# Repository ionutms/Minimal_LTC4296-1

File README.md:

# Minimal_LTC4296-1

## Overview

This repository contains a minimal KiCad design project for the Analog Devices LTC4296-1, a 5-port SPoE (Single-Pair Power over Ethernet) PSE (Power Sourcing Equipment) controller. The project includes schematic designs and PCB layout files for implementing this versatile multi-port PoE controller.

## Disclaimer

> [!NOTE]
> This project is provided "as is" and without any warranty, express or implied. For more details, please see the [LICENSE](LICENSE) file.

## About the LTC4296-1

The LTC4296-1 from Analog Devices is a 5-port SPoE (Single-Pair Power over Ethernet) PSE controller designed for building and factory automation applications. It provides power sourcing equipment functionality for IEEE 802.3cg-compliant single-pair Ethernet systems.

Key features include:

- **5 Independent PSE Ports:** Controls up to five independent PSE ports with individual monitoring and control.
- **Wide Input Supply Range:** Operates from 6 V to 60 V, supporting both 24 V and 54 V systems.
- **IEEE 802.3cg Compliant:** Supports Single-Pair Power over Ethernet (SPoE) standard with power classes 10 through 15.
- **SCCP Support:** Supports Serial Communication Classification Protocol (SCCP) with external microcontroller for PD classification.
- **SPI Interface:** SPI bus interface with PEC (Packet Error Code) protection for digital control and monitoring.
- **Advanced Protection:** Features adjustable source and return electronic circuit breakers, high-side circuit breakers with foldback, and analog current limit (ACL).
- **Low Power Consumption:** Ultra-low input supply current of 52 μA (typ) in sleep state and 51 μA (typ) in disabled state.
- **Telemetry:** Voltage, current, and temperature telemetry with per-port power-good comparators.
- **Operating Temperature Range:** -40°C to +125°C.
- **Package:** Available in a 48-lead plastic QFN package (7 mm × 7 mm).

## Project Structure

```
minimal_ltc4296-1/
├── minimal_ltc4296-1.kicad_pro                     # Project configuration file
├── minimal_ltc4296-1.kicad_sch                     # Main schematic file
├── SCCP Circuit 0.kicad_sch                        # SCCP circuit schematic
├── minimal_ltc4296-1.kicad_pcb                     # PCB layout file
├── fp-lib-table                                    # Footprint library table
├── sym-lib-table                                   # Symbol library table
├── docs/                                           # Documentation files
│   ├── bom/                                        # Bill of Materials
│   │   └── minimal_ltc4296-1_ibom.html             # Interactive BOM file
│   ├── pictures/                                   # Images and photos
│   │   ├── 1_minimal_ltc4296-1_side.png            # Side view of PCB
│   │   ├── 2_minimal_ltc4296-1_top.png             # Top view of PCB
│   │   ├── 3_minimal_ltc4296-1_bottom.png          # Bottom view of PCB
│   │   ├── 4_minimal_ltc4296-1_left.png            # Left view of PCB
│   │   ├── 5_minimal_ltc4296-1_right.png           # Right view of PCB
│   │   ├── 6_minimal_ltc4296-1_front.png           # Front view of PCB
│   │   ├── 7_minimal_ltc4296-1_back.png            # Back view of PCB
│   │   └── 8_minimal_ltc4296-1_test.png            # Test view of PCB
│   └── schematics/                                 # Schematic PDF exports
│       └── minimal_ltc4296-1_schematics.pdf        # Complete schematics PDF
└── KiCAD_Symbols_Generator/                        # Submodule for symbol generation from CSV data
```

## Project Features

This design provides a minimal implementation of the LTC4296-1 with:

- 5-port PSE controller configuration
- SPI interface for digital control
- SCCP classification support
- Per-port current monitoring and protection
- Standard footprint for the 48-lead QFN package

## Getting Started

### Prerequisites

- [KiCad EDA](https://www.kicad.org/) version 9.0 or later installed on your system
- Git (for cloning the repository and submodule management)

### Opening the Project

1. **Clone the repository** (including submodules):
   ```bash
   git clone --recursive https://github.com/ionutms/Minimal_LTC4296-1.git
   ```

   If you've already cloned the repository without submodules, initialize them with:
   ```bash
   git submodule init
   git submodule update
   ```

2. **Open the project in KiCad**:
   - Launch KiCad
   - Click "Open Existing Project"
   - Navigate to the cloned repository folder
   - Select the `minimal_ltc4296-1.kicad_pro` file

3. **Explore the design**:
   - Open the schematic editor to view the circuit design
   - Open the PCB editor to view the board layout
   - Review the symbol and footprint libraries used in the design

### Project Files

- **Main schematic**: `minimal_ltc4296-1.kicad_sch` - Contains the primary circuit design with the LTC4296-1 and support components
- **SCCP schematic**: `SCCP Circuit 0.kicad_sch` - SCCP circuit implementation for PD classification
- **PCB layout**: `minimal_ltc4296-1.kicad_pcb` - Physical board design file with proper component placement
- **Project configuration**: `minimal_ltc4296-1.kicad_pro` - KiCad project settings

## Dependencies

This project has the following dependencies:

### 1. KiCAD Symbols Generator

This repository uses [KiCAD_Symbols_Generator](https://github.com/ionutms/KiCAD_Symbols_Generator) as a submodule for custom symbol generation.

To initialize the submodule after cloning this repository:

```bash
git submodule update --init --recursive
```

### 2. 3D Models

This project requires the [3D_Models_Vault](https://github.com/ionutms/3D_Models_Vault) repository for 3D models.

#### Setup for KiCAD 9:

1. Clone the 3D models repository:
   ```bash
   git clone https://github.com/ionutms/3D_Models_Vault.git
   ```

2. In KiCAD 9, add an environment variable:
   - Variable name: `KICAD9_3D_MODELS_VAULT`
   - Variable value: Full path to where you cloned the 3D_Models_Vault repository

## Usage

After setting up the dependencies, open the project in KiCad 9 to access all features including the 3D models.

## Symbol Generator Submodule

This project includes the KiCAD_Symbols_Generator as a submodule, which provides tools for generating KiCad symbols from CSV data files. For more information on using this tool, see the [KiCAD_Symbols_Generator documentation](minimal_ltc4296-1/KiCAD_Symbols_Generator/README.md).

## Documentation

The `docs` folder contains:
- Schematic PDF exports
- Images and photos of the design

## Visuals

The following images showcase the PCB design from different perspectives:

*Top View of the PCB*

*Side View of the PCB*

*Bottom View of the PCB*

*Left View of the PCB*

*Right View of the PCB*

*Front View of the PCB*

*Back View of the PCB*

## License

This project is licensed under the MIT License - see the [LICENSE](LICENSE) file for details.

## References

- [LTC4296-1 Datasheet](https://www.analog.com/media/en/technical-documentation/data-sheets/ltc4296-1.pdf)
- [LTC4296-1 Product Page](https://www.analog.com/en/products/ltc4296-1.html)
- [KiCad EDA](https://www.kicad.org/)

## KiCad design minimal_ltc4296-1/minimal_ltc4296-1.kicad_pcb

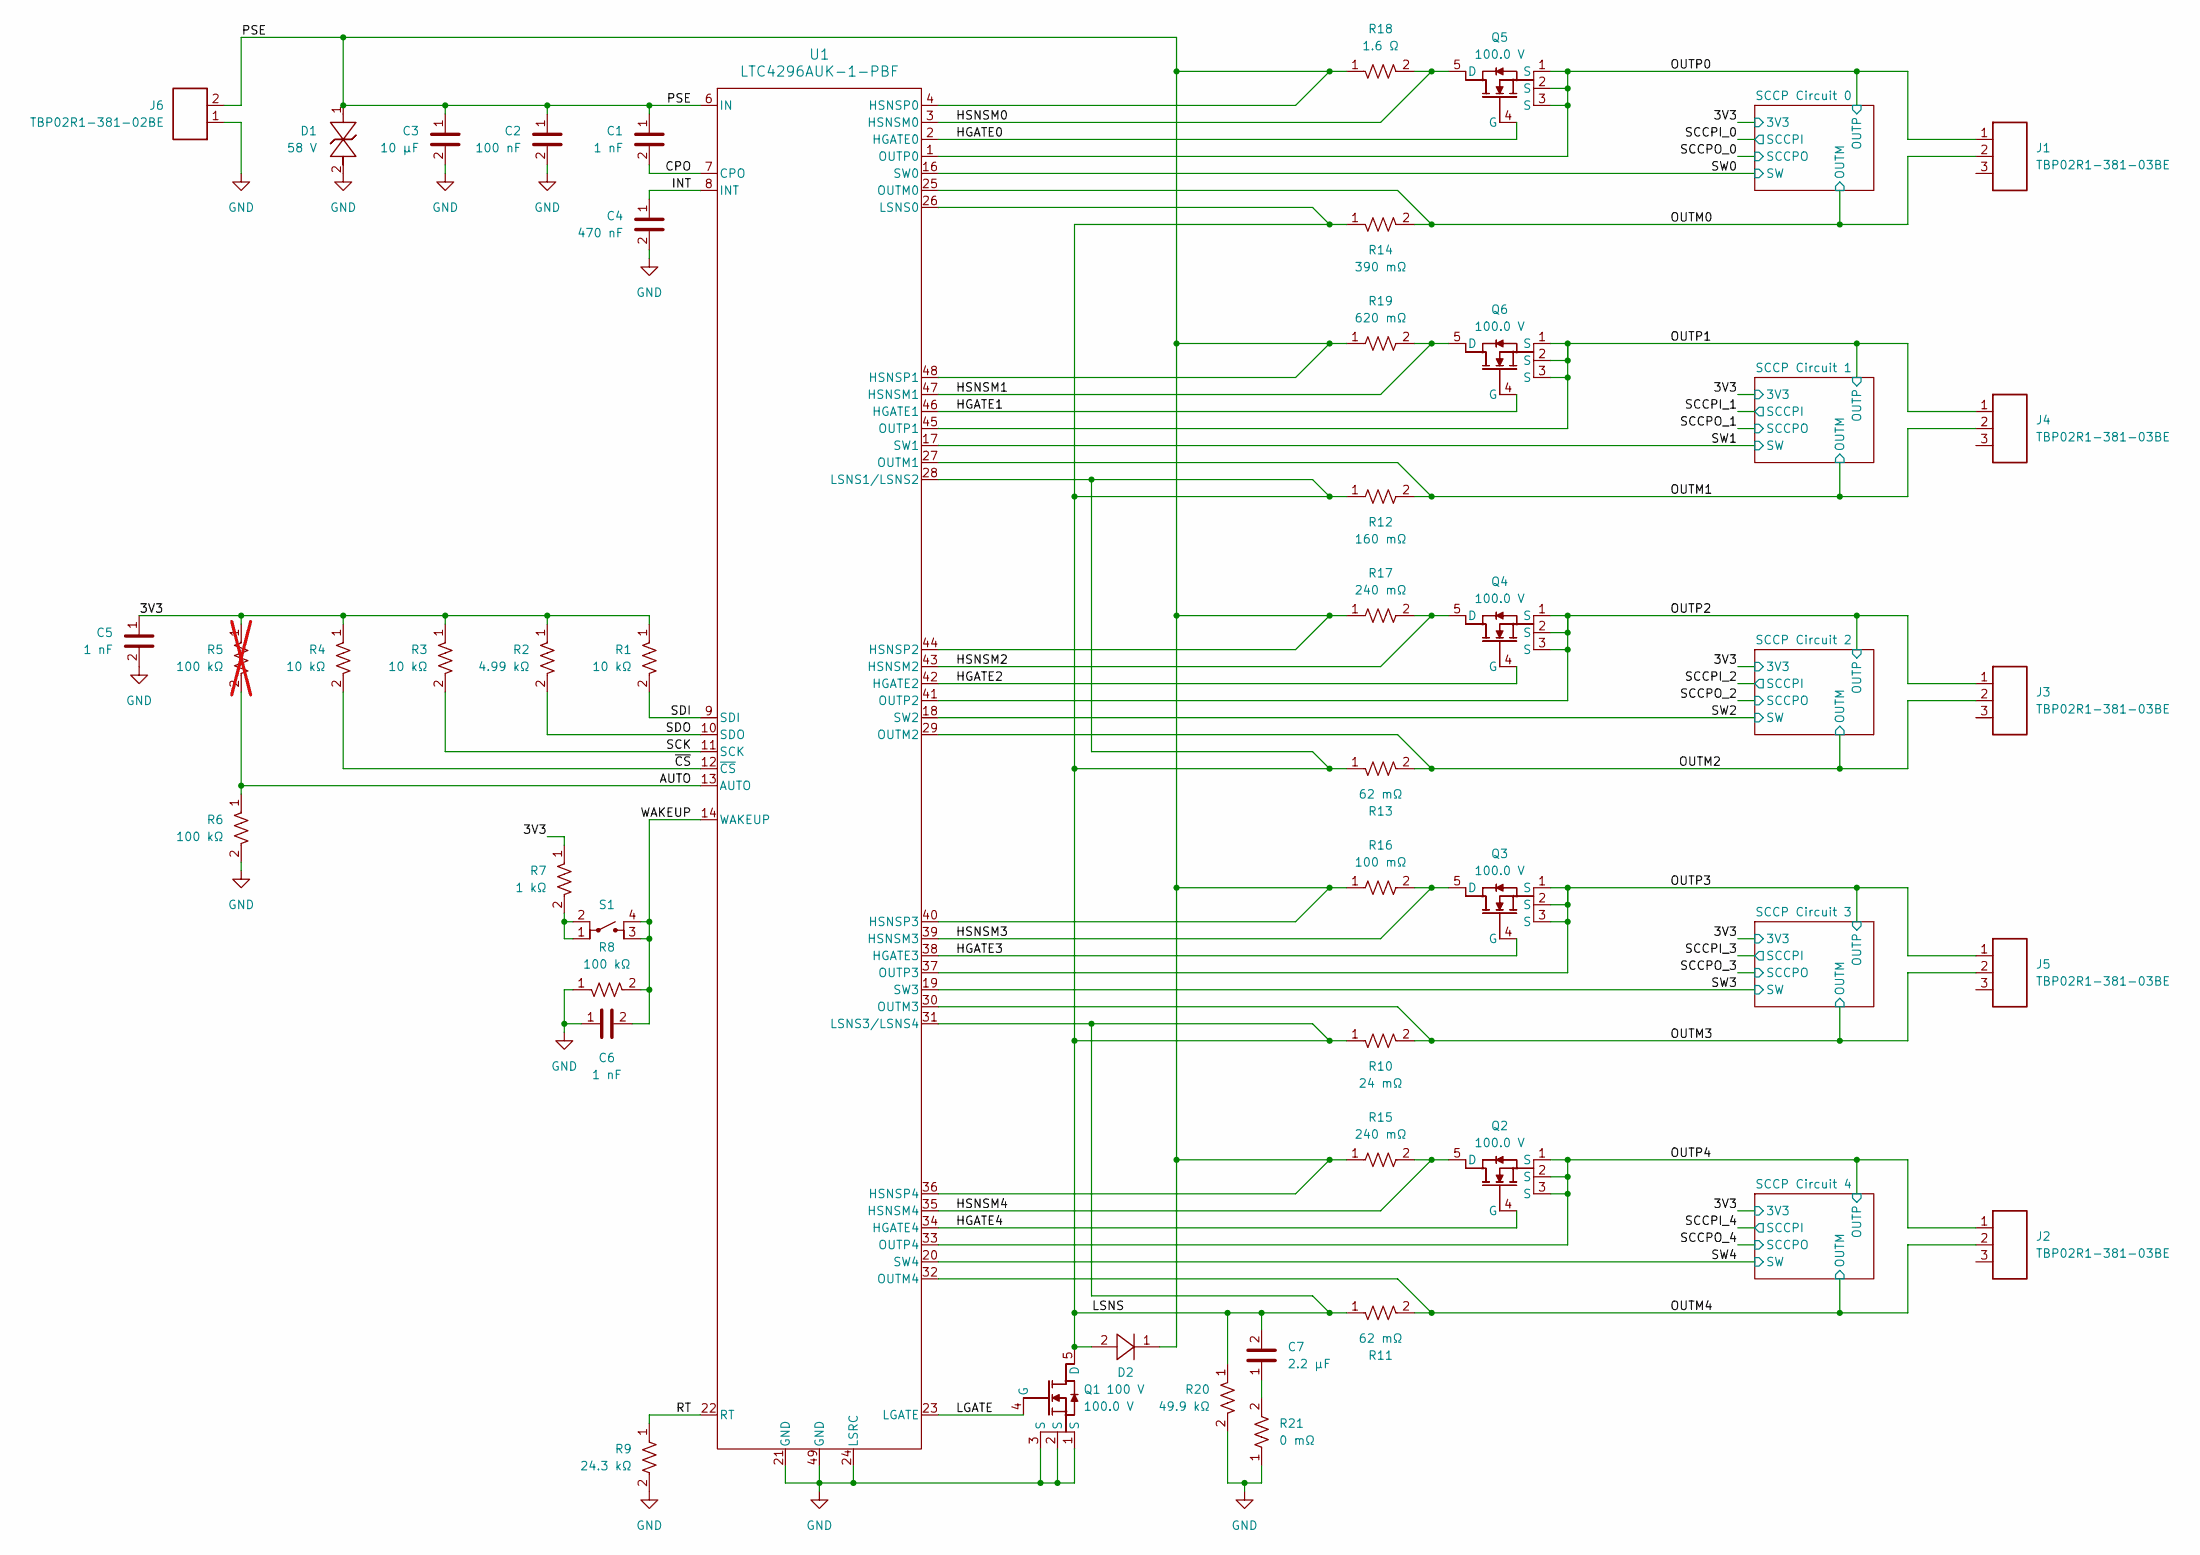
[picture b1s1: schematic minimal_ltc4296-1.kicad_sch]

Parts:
C1: 1 nF; C_0402_1005Metric; Tolerance 10%; Voltage Rating 100V; MPN C1005X7S2A102K050BB
C2: 100 nF; C_0603_1608Metric; Tolerance 10%; Voltage Rating 100V; MPN C1608X7S2A104K080AB
C3: 10 µF; C_1210_250_3225Metric; Tolerance 10%; Voltage Rating 100V; MPN GRM32EC72A106KE05L
C4: 470 nF; C_0402_1005Metric; Tolerance 10%; Voltage Rating 25V; MPN C1005X5R1E474K050BB
C5, C6: 1 nF; C_0402_1005Metric; Tolerance 10%; Voltage Rating 50V; MPN GCM155R71H102KA37D
C7: 2.2 µF; C_0805_2012Metric; Tolerance 10%; Voltage Rating 100V; MPN CGA4J1X7R2A225K125AC
D1: 58 V; DO-214AA; MPN SMBJ58CA
D2: 100 V; SMA; MPN S1B-13-F
J1, J2, J3, J4, J5: TBP02R1-381-03BE; Current Rating (A) 8.0; Voltage Rating (V) 300; MPN TBP02R1-381-03BE
J6: TBP02R1-381-02BE; Current Rating (A) 8.0; Voltage Rating (V) 300; MPN TBP02R1-381-02BE
Q1, Q2, Q4, Q5: 100.0 V; LFPAK33-8; MPN PSMN075-100MSEX
Q3, Q6: 100.0 V; LFPAK33-8; MPN PSMN040-100MSEX
R1, R3, R4: 10 kΩ; R_0402_1005Metric; Tolerance 1%; Voltage Rating 50V; MPN ERJ-2RKF1002X
R2: 4.99 kΩ; R_0402_1005Metric; Tolerance 1%; Voltage Rating 50V; MPN ERJ-2RKF4991X
R5: 100 kΩ; R_0402_1005Metric; Tolerance 1%; Voltage Rating 50V; MPN ERJ-2RKF1003X; not fitted
R6, R8: 100 kΩ; R_0402_1005Metric; Tolerance 1%; Voltage Rating 50V; MPN ERJ-2RKF1003X
R7: 1 kΩ; R_0402_1005Metric; Tolerance 1%; Voltage Rating 50V; MPN ERJ-2RKF1001X
R9: 24.3 kΩ; R_0402_1005Metric; Tolerance 1%; Voltage Rating 50V; MPN ERJ-2RKF2432X
R10: 24 mΩ; R_0612_1632Metric; Tolerance 1%; MPN ERJ-B2CFR024V
R11, R13: 62 mΩ; R_0612_1632Metric; Tolerance 1%; MPN PRL1632-R062-F-T1
R12: 160 mΩ; R_0612_1632Metric; Tolerance 1%; MPN ERJ-B2CFR16V
R14: 390 mΩ; R_0612_1632Metric; Tolerance 1%; MPN ERJ-B2BFR39V
R15, R17: 240 mΩ; R_0612_1632Metric; Tolerance 1%; MPN ERJ-B2BFR24V
R16: 100 mΩ; R_0612_1632Metric; Tolerance 1%; MPN ERJ-B2CFR10V
R18: 1.6 Ω; R_0612_1632Metric; Tolerance 1%; MPN ERJ-B2BF1R6V
R19: 620 mΩ; R_0612_1632Metric; Tolerance 1%; MPN ERJ-B2BFR62V
R20: 49.9 kΩ; R_0805_2012Metric; Tolerance 1%; Voltage Rating 150V; MPN ERJ-6ENF4992V
R21: 0 mΩ; R_0805_2012Metric; Tolerance 5%; Voltage Rating 150V; MPN ERJ-6GEY0R00V
S1: TS21-34-035-BK-160-SMT-TR; TS21; MPN TS21-34-035-BK-160-SMT-TR
U1: LTC4296AUK-1-PBF; QFN48_05-08-7073_ADI; MPN LTC4296AUK-1-PBF

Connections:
/3V3: C5.1, R1.1, R2.1, R3.1, R4.1, R5.1, R7.1; also elsewhere on the board
/AUTO: R5.2, R6.1, U1.13 (AUTO)
/CPO: C1.2, U1.7 (CPO)
/HGATE0: Q5.4 (G), U1.2 (HGATE0)
/HGATE1: Q6.4 (G), U1.46 (HGATE1)
/HGATE2: Q4.4 (G), U1.42 (HGATE2)
/HGATE3: Q3.4 (G), U1.38 (HGATE3)
/HGATE4: Q2.4 (G), U1.34 (HGATE4)
/HSNSM0: Q5.5 (D), R18.2, U1.3 (HSNSM0)
/HSNSM1: Q6.5 (D), R19.2, U1.47 (HSNSM1)
/HSNSM2: Q4.5 (D), R17.2, U1.43 (HSNSM2)
/HSNSM3: Q3.5 (D), R16.2, U1.39 (HSNSM3)
/HSNSM4: Q2.5 (D), R15.2, U1.35 (HSNSM4)
/INT: C4.1, U1.8 (INT)
/LGATE: Q1.4 (G), U1.23 (LGATE)
/LSNS: C7.2, D2.2, Q1.5 (D), R10.1, R11.1, R12.1, R13.1, R14.1, R20.1, U1.26 (LSNS0), U1.28 (LSNS1/LSNS2), U1.31 (LSNS3/LSNS4)
/OUTM0: J1.2, R14.2, U1.25 (OUTM0); also elsewhere on the board
/OUTM1: J4.2, R12.2, U1.27 (OUTM1); also elsewhere on the board
/OUTM2: J3.2, R13.2, U1.29 (OUTM2); also elsewhere on the board
/OUTM3: J5.2, R10.2, U1.30 (OUTM3); also elsewhere on the board
/OUTM4: J2.2, R11.2, U1.32 (OUTM4); also elsewhere on the board
/OUTP0: J1.1, Q5.1 (S), Q5.2 (S), Q5.3 (S), U1.1 (OUTP0); also elsewhere on the board
/OUTP1: J4.1, Q6.1 (S), Q6.2 (S), Q6.3 (S), U1.45 (OUTP1); also elsewhere on the board
/OUTP2: J3.1, Q4.1 (S), Q4.2 (S), Q4.3 (S), U1.41 (OUTP2); also elsewhere on the board
/OUTP3: J5.1, Q3.1 (S), Q3.2 (S), Q3.3 (S), U1.37 (OUTP3); also elsewhere on the board
/OUTP4: J2.1, Q2.1 (S), Q2.2 (S), Q2.3 (S), U1.33 (OUTP4); also elsewhere on the board
/PSE: C1.1, C2.1, C3.1, D1.1, D2.1, J6.2, R15.1, R16.1, R17.1, R18.1, R19.1, U1.4 (HSNSP0), U1.6 (IN), U1.36 (HSNSP4), U1.40 (HSNSP3), U1.44 (HSNSP2), U1.48 (HSNSP1)
/RT: R9.1, U1.22 (RT)
/SCK: R3.2, U1.11 (SCK)
/SDI: R1.2, U1.9 (SDI)
/SDO: R2.2, U1.10 (SDO)
/SW0: U1.16 (SW0); also elsewhere on the board
/SW1: U1.17 (SW1); also elsewhere on the board
/SW2: U1.18 (SW2); also elsewhere on the board
/SW3: U1.19 (SW3); also elsewhere on the board
/SW4: U1.20 (SW4); also elsewhere on the board
/WAKEUP: C6.2, R8.2, S1.3, S1.4, U1.14 (WAKEUP)
/~CS: R4.2, U1.12 (~CS)
GND: C2.2, C3.2, C4.2, C5.2, C6.1, D1.2, J6.1, Q1.1 (S), Q1.2 (S), Q1.3 (S), R6.2, R8.1, R9.2, R20.2, R21.1, U1.21 (GND), U1.24 (LSRC), U1.49 (GND); also elsewhere on the board
unnamed: C7.1, R21.2
unnamed: R7.2, S1.1, S1.2

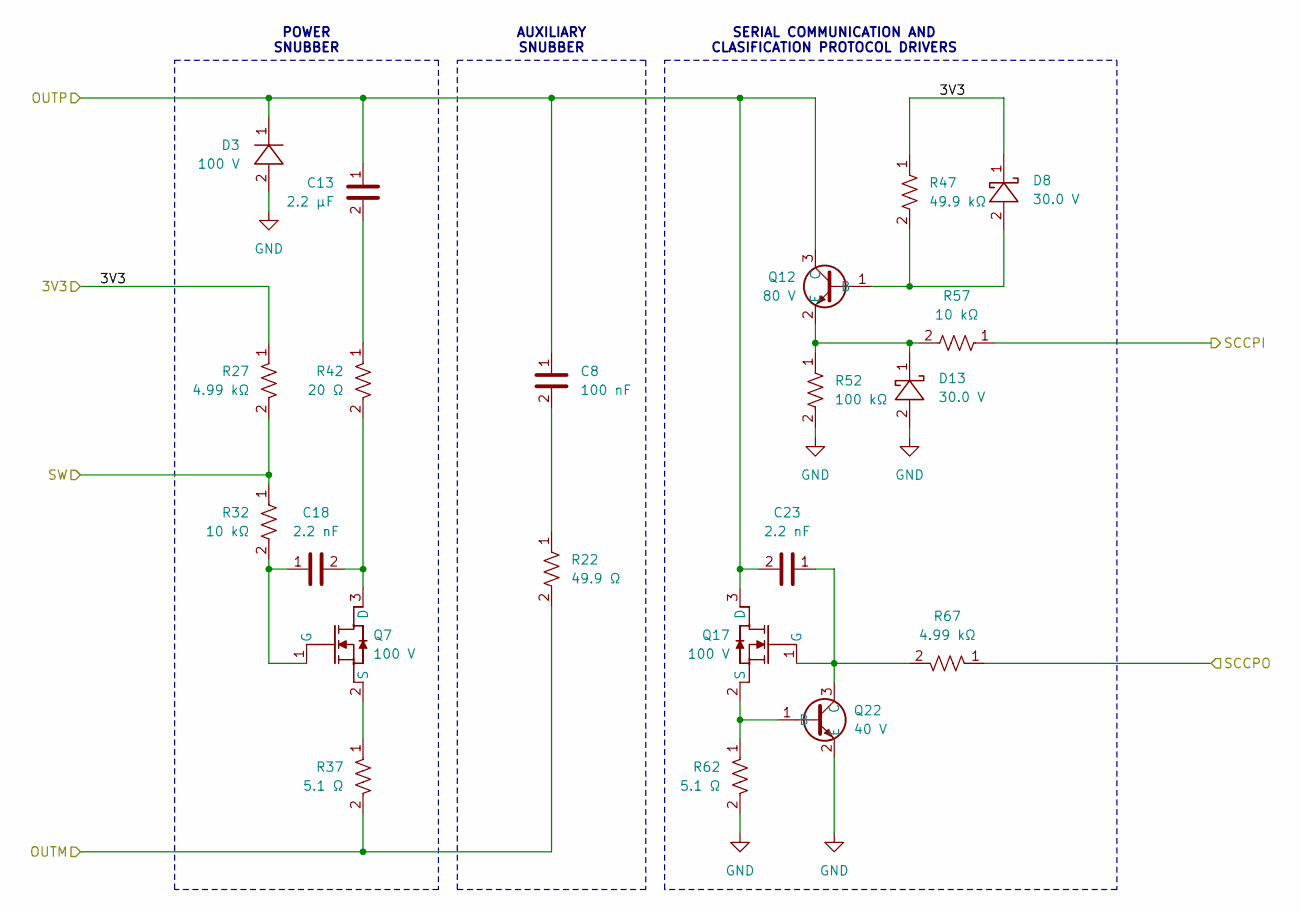
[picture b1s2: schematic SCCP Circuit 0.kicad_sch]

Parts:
C8: 100 nF; C_0603_1608Metric; Tolerance 10%; Voltage Rating 100V; MPN C1608X7S2A104K080AB
C13: 2.2 µF; C_0805_2012Metric; Tolerance 10%; Voltage Rating 100V; MPN CGA4J1X7R2A225K125AC
C18, C23: 2.2 nF; C_0402_1005Metric; Tolerance 10%; Voltage Rating 100V; MPN C1005X7S2A222K050BB
D3: 100 V; SMA; MPN S1B-13-F
D8, D13: 30.0 V; SOD323F; MPN BAT54WS-7-F
Q7, Q17: 100 V; SOT-323; MPN BSS123WQ-7-F
Q12: 80 V; SOT23-3; MPN MMBTA06-7-F
Q22: 40 V; SOT23-3; MPN MMBT3904LT3G
R22: 49.9 Ω; R_0603_1608Metric; Tolerance 1%; Voltage Rating 75V; MPN ERJ-3EKF49R9V
R27, R67: 4.99 kΩ; R_0402_1005Metric; Tolerance 1%; Voltage Rating 50V; MPN ERJ-2RKF4991X
R32, R57: 10 kΩ; R_0402_1005Metric; Tolerance 1%; Voltage Rating 50V; MPN ERJ-2RKF1002X
R37, R62: 5.1 Ω; R_1206_3216Metric; Tolerance 1%; Voltage Rating 200V; MPN RT1206FRE075R1L
R42: 20 Ω; R_1206_3216Metric; Tolerance 1%; Voltage Rating 200V; MPN RT1206FRE0720RL
R47: 49.9 kΩ; R_0402_1005Metric; Tolerance 1%; Voltage Rating 50V; MPN ERJ-2RKF4992X
R52: 100 kΩ; R_0402_1005Metric; Tolerance 1%; Voltage Rating 50V; MPN ERJ-2RKF1003X

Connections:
/3V3: D8.1, R27.1, R47.1; also elsewhere on the board
/OUTM0: R22.2, R37.2; also elsewhere on the board
/OUTP0: C8.1, C13.1, C23.2, D3.1, Q12.3 (C), Q17.3 (D); also elsewhere on the board
/SCCPI_0: R57.1
/SCCPO_0: R67.1
/SW0: R27.2, R32.1; also elsewhere on the board
GND: D3.2, D13.2, Q22.2 (E), R52.2, R62.2; also elsewhere on the board
unnamed: C8.2, R22.1
unnamed: C13.2, R42.1
unnamed: C18.2, Q7.3 (D), R42.2
unnamed: C18.1, Q7.1 (G), R32.2
unnamed: Q7.2 (S), R37.1
unnamed: D8.2, Q12.1 (B), R47.2
unnamed: D13.1, Q12.2 (E), R52.1, R57.2
unnamed: C23.1, Q17.1 (G), Q22.3 (C), R67.2
unnamed: Q17.2 (S), Q22.1 (B), R62.1

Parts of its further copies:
C9, C10, C11, C12: 100 nF; C_0603_1608Metric; Tolerance 10%; Voltage Rating 100V; MPN C1608X7S2A104K080AB
C14, C15, C16, C17: 2.2 µF; C_0805_2012Metric; Tolerance 10%; Voltage Rating 100V; MPN CGA4J1X7R2A225K125AC
C19, C20, C21, C22, C24, C25, C26, C27: 2.2 nF; C_0402_1005Metric; Tolerance 10%; Voltage Rating 100V; MPN C1005X7S2A222K050BB
D4, D5, D6, D7: 100 V; SMA; MPN S1B-13-F
D9, D10, D11, D12, D14, D15, D16, D17: 30.0 V; SOD323F; MPN BAT54WS-7-F
Q8, Q9, Q10, Q11, Q18, Q19, Q20, Q21: 100 V; SOT-323; MPN BSS123WQ-7-F
Q13, Q14, Q15, Q16: 80 V; SOT23-3; MPN MMBTA06-7-F
Q23, Q24, Q25, Q26: 40 V; SOT23-3; MPN MMBT3904LT3G
R23, R24, R25, R26: 49.9 Ω; R_0603_1608Metric; Tolerance 1%; Voltage Rating 75V; MPN ERJ-3EKF49R9V
R28, R29, R30, R31, R68, R69, R70, R71: 4.99 kΩ; R_0402_1005Metric; Tolerance 1%; Voltage Rating 50V; MPN ERJ-2RKF4991X
R33, R34, R35, R36, R58, R59, R60, R61: 10 kΩ; R_0402_1005Metric; Tolerance 1%; Voltage Rating 50V; MPN ERJ-2RKF1002X
R38, R39, R40, R41, R63, R64, R65, R66: 5.1 Ω; R_1206_3216Metric; Tolerance 1%; Voltage Rating 200V; MPN RT1206FRE075R1L
R43, R44, R45, R46: 20 Ω; R_1206_3216Metric; Tolerance 1%; Voltage Rating 200V; MPN RT1206FRE0720RL
R48, R49, R50, R51: 49.9 kΩ; R_0402_1005Metric; Tolerance 1%; Voltage Rating 50V; MPN ERJ-2RKF4992X
R53, R54, R55, R56: 100 kΩ; R_0402_1005Metric; Tolerance 1%; Voltage Rating 50V; MPN ERJ-2RKF1003X

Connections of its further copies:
/3V3: D9.1, D10.1, D11.1, D12.1, R28.1, R29.1, R30.1, R31.1, R48.1, R49.1, R50.1, R51.1; also elsewhere on the board
/OUTM1: R23.2, R38.2; also elsewhere on the board
/OUTM2: R24.2, R39.2; also elsewhere on the board
/OUTM3: R25.2, R40.2; also elsewhere on the board
/OUTM4: R26.2, R41.2; also elsewhere on the board
/OUTP1: C9.1, C14.1, C24.2, D4.1, Q13.3 (C), Q18.3 (D); also elsewhere on the board
/OUTP2: C10.1, C15.1, C25.2, D5.1, Q14.3 (C), Q19.3 (D); also elsewhere on the board
/OUTP3: C11.1, C16.1, C26.2, D6.1, Q15.3 (C), Q20.3 (D); also elsewhere on the board
/OUTP4: C12.1, C17.1, C27.2, D7.1, Q16.3 (C), Q21.3 (D); also elsewhere on the board
/SCCPI_1: R58.1
/SCCPI_2: R59.1
/SCCPI_3: R60.1
/SCCPI_4: R61.1
/SCCPO_1: R68.1
/SCCPO_2: R69.1
/SCCPO_3: R70.1
/SCCPO_4: R71.1
/SW1: R28.2, R33.1; also elsewhere on the board
/SW2: R29.2, R34.1; also elsewhere on the board
/SW3: R30.2, R35.1; also elsewhere on the board
/SW4: R31.2, R36.1; also elsewhere on the board
GND: D4.2, D5.2, D6.2, D7.2, D14.2, D15.2, D16.2, D17.2, Q23.2 (E), Q24.2 (E), Q25.2 (E), Q26.2 (E), R53.2, R54.2, R55.2, R56.2, R63.2, R64.2, R65.2, R66.2; also elsewhere on the board
unnamed: C9.2, R23.1
unnamed: C10.2, R24.1
unnamed: C11.2, R25.1
unnamed: C12.2, R26.1
unnamed: C14.2, R43.1
unnamed: C15.2, R44.1
unnamed: C16.2, R45.1
unnamed: C17.2, R46.1
unnamed: C19.2, Q8.3 (D), R43.2
unnamed: C19.1, Q8.1 (G), R33.2
unnamed: Q8.2 (S), R38.1
unnamed: C20.2, Q9.3 (D), R44.2
unnamed: C20.1, Q9.1 (G), R34.2
unnamed: Q9.2 (S), R39.1
unnamed: C21.2, Q10.3 (D), R45.2
unnamed: C21.1, Q10.1 (G), R35.2
unnamed: Q10.2 (S), R40.1
unnamed: C22.2, Q11.3 (D), R46.2
unnamed: C22.1, Q11.1 (G), R36.2
unnamed: Q11.2 (S), R41.1
unnamed: D9.2, Q13.1 (B), R48.2
unnamed: D14.1, Q13.2 (E), R53.1, R58.2
unnamed: D10.2, Q14.1 (B), R49.2
unnamed: D15.1, Q14.2 (E), R54.1, R59.2
unnamed: D11.2, Q15.1 (B), R50.2
unnamed: D16.1, Q15.2 (E), R55.1, R60.2
unnamed: D12.2, Q16.1 (B), R51.2
unnamed: D17.1, Q16.2 (E), R56.1, R61.2
unnamed: C24.1, Q18.1 (G), Q23.3 (C), R68.2
unnamed: Q18.2 (S), Q23.1 (B), R63.1
unnamed: C25.1, Q19.1 (G), Q24.3 (C), R69.2
unnamed: Q19.2 (S), Q24.1 (B), R64.1
unnamed: C26.1, Q20.1 (G), Q25.3 (C), R70.2
unnamed: Q20.2 (S), Q25.1 (B), R65.1
unnamed: C27.1, Q21.1 (G), Q26.3 (C), R71.2
unnamed: Q21.2 (S), Q26.1 (B), R66.1

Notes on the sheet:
POWER SNUBBER
SERIAL COMMUNICATION AND CLASIFICATION PROTOCOL DRIVERS
AUXILIARY SNUBBER

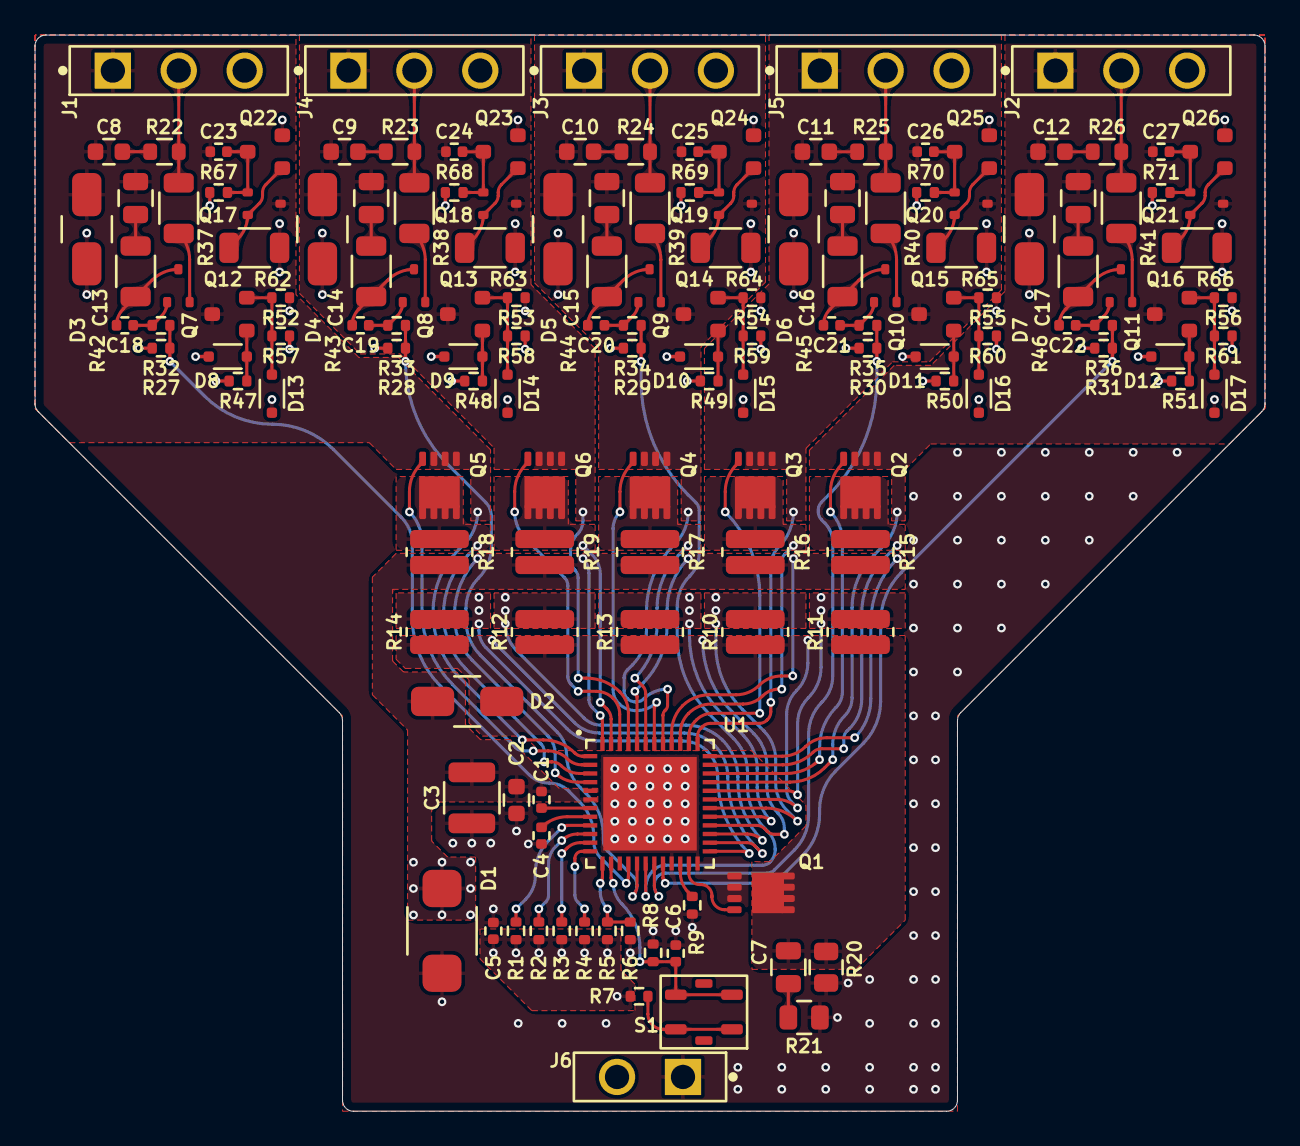
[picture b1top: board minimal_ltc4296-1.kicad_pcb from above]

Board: 4 copper layers, 71.1 x 62.2 mm, 149 parts (0 on the bottom side), 86 nets.

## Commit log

2026-01-31 Add KiCad project files for minimal LTC4296-1 board
2026-01-31 Add KiCad Symbols Generator submodule
2026-01-31 Add KiCad library tables (fp-lib-table and sym-lib-table)
2026-01-31 Update KiCad project files (PCB layout, schematic, and project settings)
2026-01-31 chore: update workflows and kicad config from central repository
2026-01-31 Update KiCad documentation for minimal_ltc4296-1 (schematics and PCB renders)
2026-01-31 Update KiCad project files
2026-01-31 Update KiCAD project files and generator
2026-01-31 Update KiCAD Symbols Generator
2026-02-01 Update KiCAD files and submodule
2026-02-01 Update KiCAD Symbols Generator submodule
2026-02-03 Update KiCAD schematic and PCB files
2026-02-04 Update PCB and schematic files
2026-02-05 Update KiCad PCB and schematic files
2026-02-06 Update PCB file
2026-02-07 Update KiCAD files and generator
2026-02-07 Update PCB layout and schematic, refresh symbol library
2026-02-08 Update PCB layout and schematic
2026-02-08 Update PCB layout
2026-02-09 Update PCB and schematic files, and KiCAD symbols generator
2026-02-11 Update KiCad PCB file
2026-02-14 Update KiCad project settings and PCB layout
2026-02-17 Update KiCad project files and add SCCP Circuit 0 schematic
2026-02-19 Update KiCad schematic, PCB, and symbol libraries with SCCP circuit changes
2026-02-19 Update KiCAD_Symbols_Generator submodule
2026-02-21 Update KiCad config zoom and pan settings
2026-02-21 Update KiCad config pan setting
2026-03-03 Update README with accurate LTC4296-1 specifications
2026-03-03 Remove test view configuration and image
2026-03-03 Add all PCB view images to README
